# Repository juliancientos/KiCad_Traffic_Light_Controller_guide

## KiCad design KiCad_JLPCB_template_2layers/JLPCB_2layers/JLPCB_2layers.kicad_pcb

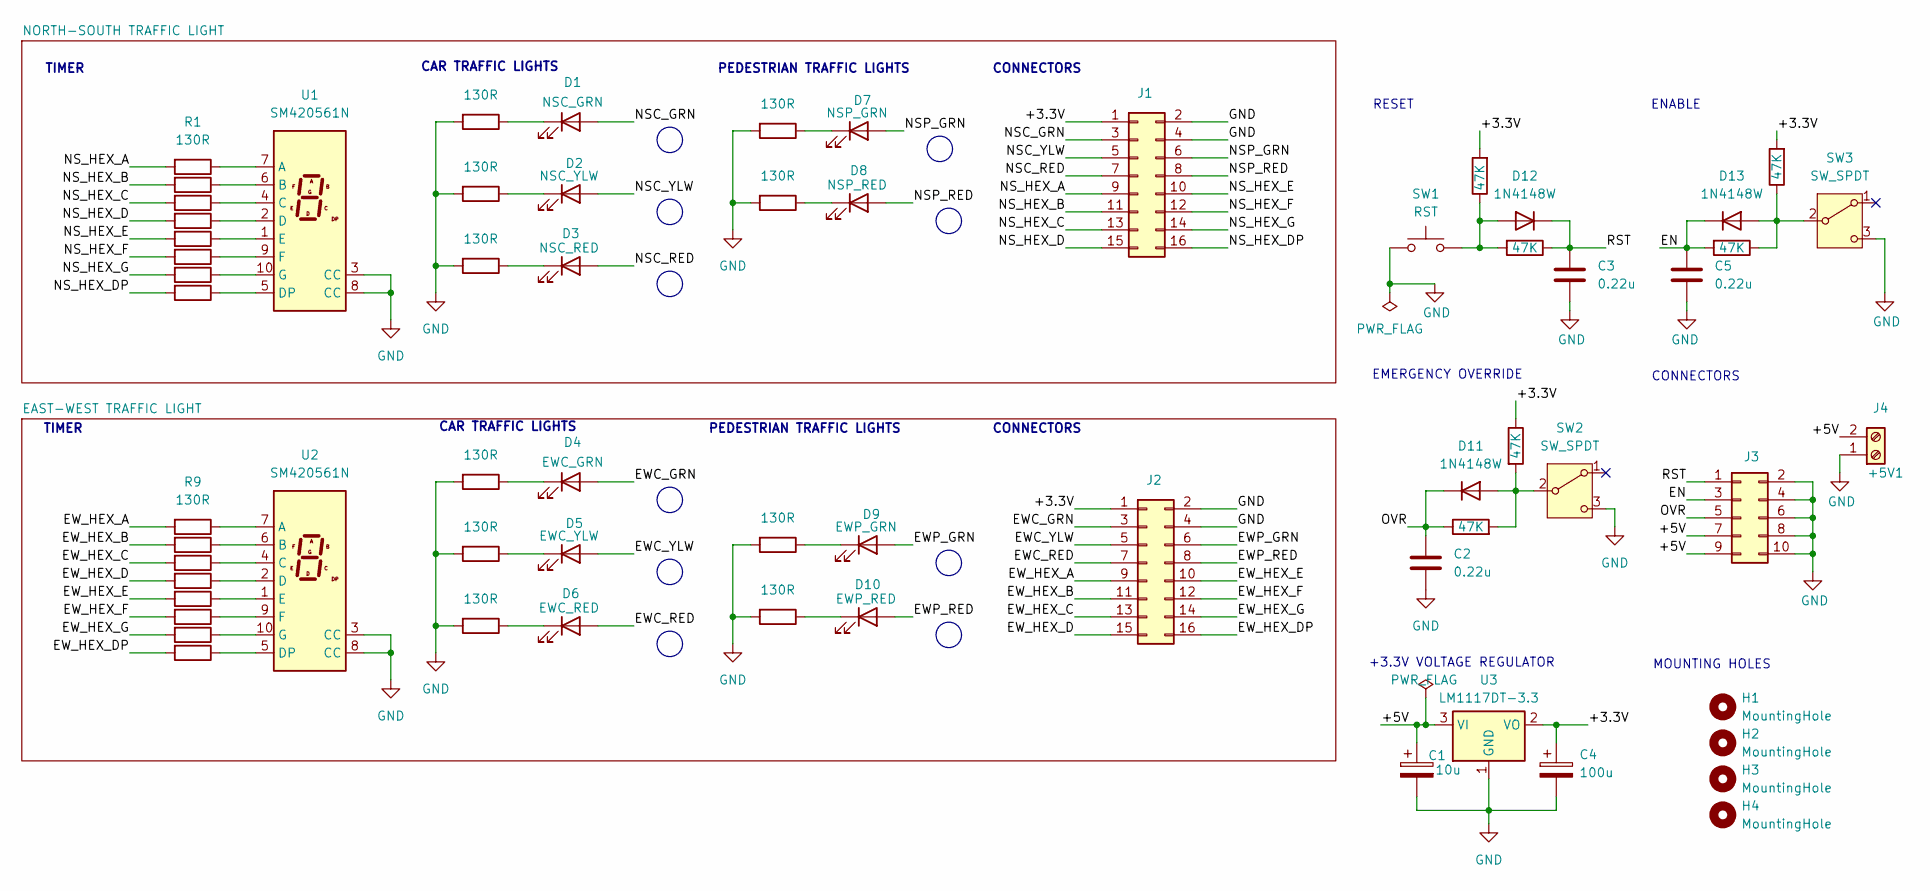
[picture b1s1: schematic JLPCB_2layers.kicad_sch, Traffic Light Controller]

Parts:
+5V1: J4; Terminal_Block_5mm
C1: 10u; CP_Elec_4x5.3
C2, C3, C5: 0.22u; C_1206_3216Metric_Pad1.33x1.80mm_HandSolder
C4: 100u; CP_Elec_6.3x5.8
D1: NSC_GRN; LED_D5.0mm
D2: NSC_YLW; LED_D5.0mm
D3: NSC_RED; LED_D5.0mm
D4: EWC_GRN; LED_D5.0mm
D5: EWC_YLW; LED_D5.0mm
D6: EWC_RED; LED_D5.0mm
D7: NSP_GRN; LED_D5.0mm
D8: NSP_RED; LED_D5.0mm
D9: EWP_GRN; LED_D5.0mm
D10: EWP_RED; LED_D5.0mm
D11, D12, D13: 1N4148W; D_SOD-123
H1, H2, H3, H4: MountingHole; MountingHole_2.2mm_M2
J1, J2: Conn_02x08_Odd_Even; PinHeader_2x08_P2.54mm_Vertical
J3: Conn_02x05_Odd_Even; PinHeader_2x05_P2.54mm_Vertical
R1, R2, R3, R4, R5, R6, R7, R8, R9, R10, R11, R12, R13, R14, R15, R16, R17, R18, R19, R20, R21, R22, R23, R24, R25, R26: 130R; R_1206_3216Metric_Pad1.30x1.75mm_HandSolder
R27, R28, R29, R30, R31, R32: 47K; R_1206_3216Metric_Pad1.30x1.75mm_HandSolder
SW1: RST; tact_switch_5mm
SW2, SW3: SW_SPDT; slide_switch_2.54mm
U1, U2: SM420561N; 7SegmentLED_LTS6760_LTS6780
U3: LM1117DT-3.3; SOT-223

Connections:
/+3.3V: C4.1, J1.1, J2.1, R27.2, R30.1, R32.2, U3.2 (VO)
/+5V: +5V1.2, C1.1, J3.7, J3.9, U3.3 (VI)
/EN: C5.1, D13.1 (K), J3.3, R31.2
/EWC_GRN: D4.2 (A), J2.3
/EWC_RED: D6.2 (A), J2.7
/EWC_YLW: D5.2 (A), J2.5
/EWP_GRN: D9.2 (A), J2.6
/EWP_RED: D10.2 (A), J2.8
/EW_HEX_A: J2.9, R9.2
/EW_HEX_B: J2.11, R10.2
/EW_HEX_C: J2.13, R11.2
/EW_HEX_D: J2.15, R12.2
/EW_HEX_DP: J2.16, R16.2
/EW_HEX_E: J2.10, R13.2
/EW_HEX_F: J2.12, R14.2
/EW_HEX_G: J2.14, R15.2
/NSC_GRN: D1.2 (A), J1.3
/NSC_RED: D3.2 (A), J1.7
/NSC_YLW: D2.2 (A), J1.5
/NSP_GRN: D7.2 (A), J1.6
/NSP_RED: D8.2 (A), J1.8
/NS_HEX_A: J1.9, R1.2
/NS_HEX_B: J1.11, R2.2
/NS_HEX_C: J1.13, R3.2
/NS_HEX_D: J1.15, R4.2
/NS_HEX_DP: J1.16, R8.2
/NS_HEX_E: J1.10, R5.2
/NS_HEX_F: J1.12, R6.2
/NS_HEX_G: J1.14, R7.2
/OVR: C2.1, D11.1 (K), J3.5, R28.1
/RST: C3.1, D12.1 (K), J3.1, R29.1
GND: +5V1.1, C1.2, C2.2, C3.2, C4.2, C5.2, J1.2, J1.4, J2.2, J2.4, J3.2, J3.4, J3.6, J3.8, J3.10, R17.2, R18.2, R19.2, R20.2, R21.2, R22.2, R23.2, R24.2, R25.2, R26.2, SW1.1, SW2.3 (C), SW3.3 (C), U1.3 (CC), U1.8 (CC), U2.3 (CC), U2.8 (CC), U3.1 (GND)
unnamed: D1.1 (K), R17.1
unnamed: D2.1 (K), R18.1
unnamed: D3.1 (K), R19.1
unnamed: D4.1 (K), R20.1
unnamed: D5.1 (K), R21.1
unnamed: D6.1 (K), R22.1
unnamed: D7.1 (K), R23.1
unnamed: D8.1 (K), R24.1
unnamed: D9.1 (K), R25.1
unnamed: D10.1 (K), R26.1
unnamed: D11.2 (A), R28.2, R30.2, SW2.2 (B)
unnamed: D12.2 (A), R27.1, R29.2, SW1.2
unnamed: D13.2 (A), R31.1, R32.1, SW3.2 (B)
unnamed: R1.1, U1.7 (A)
unnamed: R2.1, U1.6 (B)
unnamed: R3.1, U1.4 (C)
unnamed: R4.1, U1.2 (D)
unnamed: R8.1, U1.5 (DP)
unnamed: R5.1, U1.1 (E)
unnamed: R6.1, U1.9 (F)
unnamed: R7.1, U1.10 (G)
unnamed: R9.1, U2.7 (A)
unnamed: R10.1, U2.6 (B)
unnamed: R11.1, U2.4 (C)
unnamed: R12.1, U2.2 (D)
unnamed: R16.1, U2.5 (DP)
unnamed: R13.1, U2.1 (E)
unnamed: R14.1, U2.9 (F)
unnamed: R15.1, U2.10 (G)

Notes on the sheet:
ENABLE
CAR TRAFFIC LIGHTS
CONNECTORS
TIMER
RESET
MOUNTING HOLES
+3.3V VOLTAGE REGULATOR
PEDESTRIAN TRAFFIC LIGHTS
EMERGENCY OVERRIDE

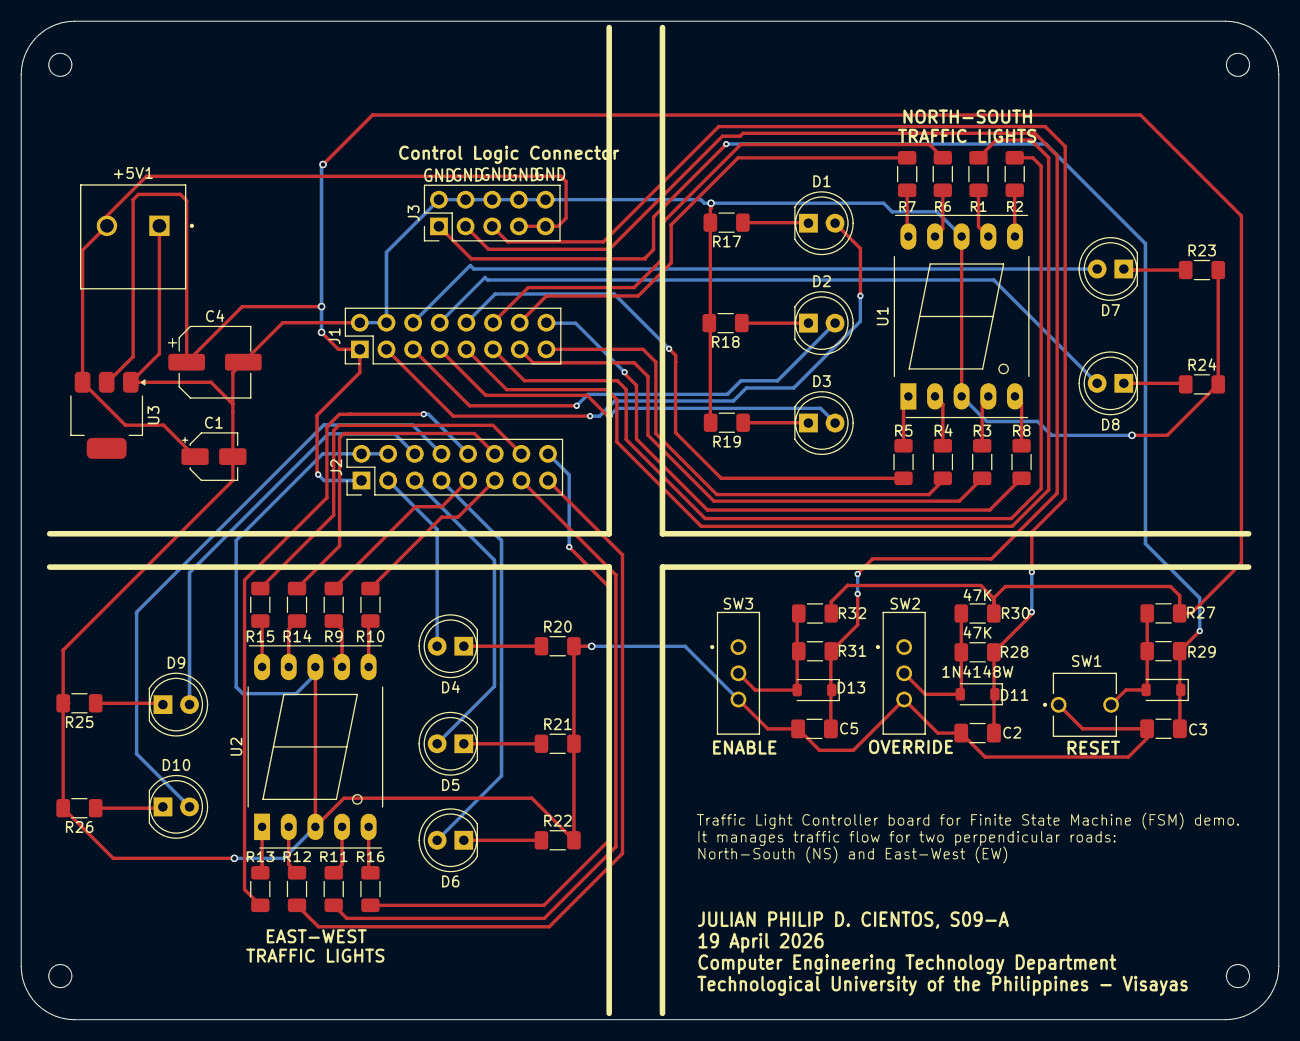
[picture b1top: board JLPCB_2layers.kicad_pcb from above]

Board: 2 copper layers, 119.9 x 95.2 mm, 64 parts (0 on the bottom side), 61 nets.

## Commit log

2026-04-21 Traffic Controller Finished Design
2026-04-22 Trafiic Controller Finished Design
2026-04-22 Conversion of file to 10.0 to 9.0
